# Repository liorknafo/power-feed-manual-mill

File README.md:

# power-feed-manual-mill

A stepper-motor X-axis power feed for a **SIEG X3.5D** mill.

## Features
- **Speed:** a speed dial and an OLED showing mm/min.
- **Mode switch** (3 positions): LEFT, STOP, RIGHT.
- **Rapid traverse button.**
- **Clutch:** a home-made **electromagnetic tooth clutch**. With the switch on STOP the handwheel turns freely, as it does with no power.
- **Safety:**
  - a hardware E-stop interlock;
  - limit switches;
  - stall detection from an encoder on the leadscrew.

## What is where

| Folder | What | Start here |
|---|---|---|
| `docs/` | The spec, plus notes about the mill | `docs/design.md`, `docs/mill.md` |
| `hardware/` | KiCad 9 schematic + 4-layer 100×100 mm PCB, order files | `hardware/README.md`, `hardware/fab/README.md` |
| `firmware/` | Rust firmware for the RP2040 (Embassy). Core logic is unit-tested on the PC | `firmware/README.md` |
| `mechanical/solidcraft/` | The CAD, in SolidCraft: one parametric design per part, the clutch and feed-unit assemblies, checks, renders, the mains tray's flat patterns | `mechanical/README.md`, `mechanical/solidcraft/README.md` |
| `mechanical/clutch/` | Tooth clutch: machining sheet | `mechanical/clutch/MACHINING.md` |
| `mechanical/feed_unit/` | The whole power feed in one box at the left table end: plate, 2:1 belt, leadscrew stub, encoder, clutch module, motor, controller PCB and control panel | `mechanical/feed_unit/FEED_UNIT.md` |

## Status

| Part | State |
|---|---|
| Schematic | Done: bare RP2040 (flash, crystal, USB-C with ESD, 3.3 V LDO), TMC5160 power stage, clutch driver, E-stop interlock. ERC clean, netlist checked, independently reviewed |
| PCB | **Ready to order.** 4 layers, 100 × 100 mm. Independently reviewed over 4 rounds (power stage, RP2040 layout, assembly). DRC 0 errors with schematic parity (11 cosmetic silkscreen warnings). Gerbers, BOM, CPL in `hardware/fab/` |
| Firmware | Builds for the RP2040; 48 passing tests. Flashable with the box closed: **USB FLASH** menu item + end-wall USB-C (UF2), or the end-wall SWD port with a Debug Probe (recovers anything). Needs bench commissioning (`firmware/README.md`) |
| CAD | In SolidCraft (`mechanical/solidcraft/`), migrated from the build123d model part by part and checked against it (identical apart from true arcs where the old model used polylines, and real bends in the sheet-metal tray). Interference, mains separation, door swing and print fit re-checked in SolidCraft |
| Clutch CAD | Ready to machine, after you measure the motor shaft length. Independently reviewed for fit and for machinability on a 3-axis CNC + manual lathe/mill (teeth: one 60° chamfer-mill pass per flank). Magnetic sizing must be bench-calibrated |
| Feed unit CAD | Structure reviewed: Oldham drive, circlip bearing stack, encoder adapter, guard, drawbolt tensioner. **Mill-side dimensions are placeholders until measured** |
| Housing (one box: drive + PCB + controls + 36 V supply) | **Ready to print.** Compact, rounded PETG (116 × 204 × 262 mm), built-in LRS-150-36 supply (the only 36 V Mean Well on Amazon that ships to Israel) and fused, switched IEC inlet in an earthed aluminium mains tray (mains part independently safety-reviewed: wiring room, separation, fixing, earthing, assembly order); USB-C, BOOT/RESET and SWD on the end wall: a shell, a hood with the controls, a bottom door (the clutch/motor module and the mains tray go in and come out from below) and an end cap that slides on last and holds the door's far end, each one print on a Prusa MK3S with no supports; the PCB lies above the motor. Independently reviewed (printability, assembly, tool access, plugs, inserts). See FEED_UNIT.md → "Housing" |

## What you need to do

1. **Measure the mill** (`docs/mill.md` → "Unknown"):
   - leadscrew pitch;
   - the left leadscrew end and its drive slot;
   - where the plate can bolt to the table end;
   - clearances at full travel.

   Enter the values in the SolidCraft part files that use them (`mechanical/solidcraft/README.md` → "Measure first"
   lists each value's parameter and files), update the assemblies' links and run the checks.
2. **Measure the motor:** shaft length beyond the flange and the pilot diameter. Set `shaft_len` and `pilot_d` the same way.
3. **Order the PCB:**
   - upload `hardware/fab/power-feed-gerbers.zip` to JLCPCB: 4 layers, 1.6 mm, 1 oz outer copper (standard; 2 oz breaks the fine-pitch spacing);
   - stencil plus the BOM/CPL for assembly, or reflow it yourself;
   - everything is SMD on the top side, including the RP2040 (QFN-56, 0.4 mm pitch: use the stencil);
   - hand-solder only the SWD header J3, and trim its pins flush underneath (they face the motor);
   - USB-C (J4) shell pegs: solder from below with little solder, fit the panel IDC header J6 last and check it sits flat.
4. **Make the clutch** (`MACHINING.md`). Check the mated teeth (pole gap 0.15 ± 0.05), then calibrate on the bench: pull force and
   cam-out torque against hold current.
5. **Print the housing** (shell + hood, PETG on the MK3S; `FEED_UNIT.md` → "Housing") and machine the feed-unit parts (`FEED_UNIT.md`).
6. **Flash and commission:** follow `firmware/README.md` → *Commissioning*, in order, before mounting on the mill.

## Rebuilding things
```sh
python3 hardware/tools/check_schematic.py                 # schematic: ERC + netlist check
python3 hardware/tools/check_pcb.py                       # PCB: DRC + schematic parity
(cd firmware/feed-core && cargo test)                     # logic tests
(cd firmware/feed-app && cargo build --release)           # firmware
(cd mechanical/solidcraft && solidcraft-cli run clutch.build.json --save clutch.sc)        # clutch assembly
(cd mechanical/solidcraft && solidcraft-cli run feed_unit.build.json --save feed_unit.sc)  # whole unit
python3 mechanical/solidcraft/tools/check.py        # interference (clutch engaged + released), mains separation, door, print fit
sh mechanical/solidcraft/tools/render.sh            # renders
```

The CAD needs SolidCraft 0.40 or later (`solidcraft-cli` on the PATH); edit the parts in the SolidCraft app.

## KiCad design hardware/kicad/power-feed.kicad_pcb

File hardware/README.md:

# Hardware — controller PCB

```
hardware/
  tools/build_schematic.py   circuit description (source of truth for now)
  tools/kicad_gen.py         generator: Python parts/nets -> KiCad 9 schematic
  tools/check_schematic.py   ERC + netlist-vs-intent + footprint check
  tools/sexp.py              S-expression reader/writer
  kicad/                     generated KiCad project (open power-feed.kicad_pro)
```

## Regenerate and check

```sh
python3 hardware/tools/check_schematic.py    # builds, runs KiCad ERC, compares netlist
```

The check:
- runs KiCad's ERC and fails on any error not in the reviewed allow-list;
- exports the netlist and requires every net to match the intended connections exactly;
- lists parts whose footprint is missing.

## How the generated sheets look

Every pin gets a short wire stub and a net label; there are no long wires. Connectivity therefore comes only from net names, which keeps the generated schematic correct by construction. Labels used on more than one sheet are global labels; power nets use power symbols.

## Workflow

While the circuit is still changing, edit `build_schematic.py` and regenerate. Edits made in the KiCad GUI are overwritten on regeneration. Once the circuit is frozen for layout, stop regenerating, and from then on edit the schematic in KiCad directly.

Sheets: power input and 5 V buck · TMC5160 driver · RP2040 (flash, crystal, USB-C, 3.3 V LDO) and E-stop interlock · clutch driver · panel I/O. See `docs/design.md` §4 for the pin map and §7.6 for the clutch driver.

## PCB

```sh
KPY=/Applications/KiCad/KiCad.app/Contents/Frameworks/Python.framework/Versions/Current/bin/python3
$KPY hardware/tools/build_pcb.py --route   # place, planes, Freerouting, power pours, GND stitching
$KPY hardware/tools/fix_planes.py          # vias to planes for anything the router left
$KPY hardware/tools/finish_pcb.py          # bridge pours for the last same-net gaps
$KPY hardware/tools/manual_fixes.py        # hand re-routes of the spots the scripts could not close (documented inside)
$KPY hardware/tools/silk_cleanup.py        # passives' refs to F.Fab, relocate the rest, connector labels + title
python3 hardware/tools/check_pcb.py        # KiCad DRC + schematic parity
python3 hardware/tools/export_fab.py       # Gerbers, drills, BOM, CPL, zip -> hardware/fab/
hardware/tools/render_pcb.sh               # 2D layer PNGs; 3D: kicad-cli pcb render
```

The saved `kicad/power-feed.kicad_pcb` is the master now: `build_pcb.py` rebuilds from scratch and throws away
the routing, so do not rerun it unless the schematic changes. `manual_fixes.py` and `silk_cleanup.py` are
idempotent and only touch the items they describe.

- **Board:** 100×100 mm, 4 layers: F.Cu signals + GND pour, In1 GND plane, In2 split +36V (power area) / +3V3, B.Cu signals + GND pour.
- **Autorouter:** Freerouting 2.4.1, run on Java 25. Set `FREEROUTING_JAR` to point at your copy.
- **Order** with standard 1 oz outer copper: the widths are sized for 1 oz at ~3.5 A RMS motor phases, and 2 oz would break the 0.15 mm fine-pitch spacing.

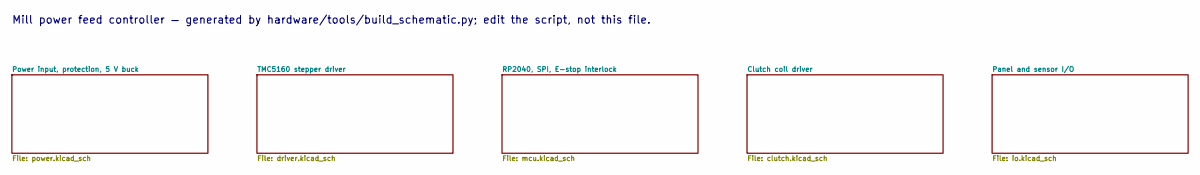
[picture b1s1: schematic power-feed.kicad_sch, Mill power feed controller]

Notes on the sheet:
Mill power feed controller — generated by hardware/tools/build_schematic.py; edit the script, not this file.

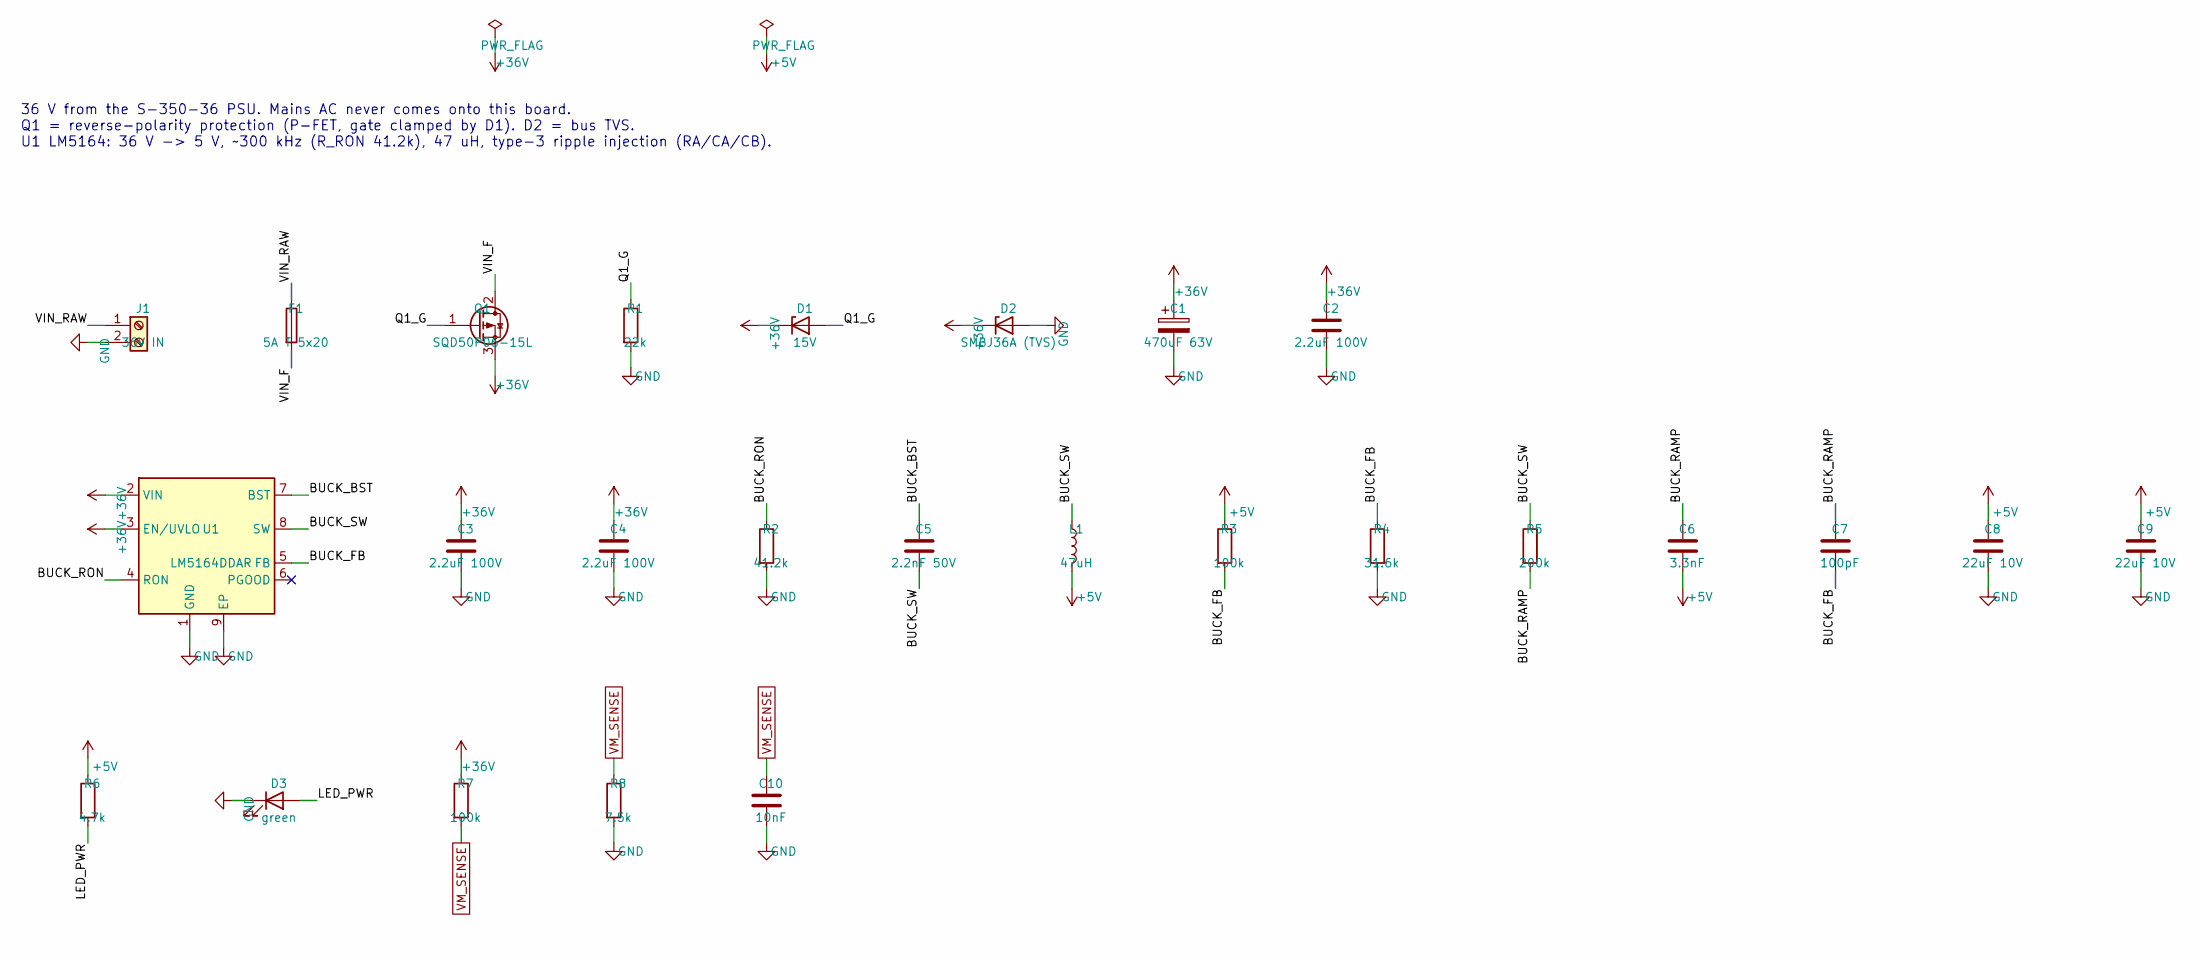
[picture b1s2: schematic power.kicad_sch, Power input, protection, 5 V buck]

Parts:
C1: 470uF 63V; CP_Radial_D12.5mm_P5.00mm; MPN Panasonic EEUFR1J471; LCSC C407954
C2, C3, C4: 2.2uF 100V; C_1210_3225Metric; MPN Murata GRM32ER72A225KA35L; LCSC C86054
C5: 2.2nF 50V; C_0603_1608Metric; MPN FH 0603B222K500NT; LCSC C1604
C6: 3.3nF; C_0603_1608Metric; MPN Samsung CL10B332KB8NNNC; LCSC C1613
C7: 100pF; C_0603_1608Metric; MPN Samsung CL10C101JB8NNNC; LCSC C14858
C8, C9: 22uF 10V; C_1206_3216Metric; MPN Samsung CL31A226KAHNNNE; LCSC C12891
C10: 10nF; C_0603_1608Metric; MPN FH 0603B103K500NT; LCSC C57112
D1: 15V; D_SOD-123; MPN onsemi MMSZ5245BT1G; LCSC C129730
D2: SMBJ36A (TVS); D_SMB; MPN SMBJ36A; LCSC C114001
D3: green; LED_0603_1608Metric; MPN KENTO KT-0603G; LCSC C12624
F1: 5A T 5x20; Fuseholder_XC_BLX-A_5x20mm_P22.00mm; MPN BLX-A holder + Littelfuse 0215005.MXP (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; LCSC C3131
J1: 36V IN; PhoenixContact_MSTBA_2,5_2-G-5,08_1x02_P5.08mm_Horizontal; MPN KF2EDGR-5.08-2P (+ plug KF2EDGK-5.08-2P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; LCSC C441204
L1: 47uH; L_TDK_VLS6045EX_VLS6045AF; MPN TDK VLS6045EX-470M; LCSC C404505
Q1: SQD50P06-15L; TO-252-2; MPN SQD50P06-15L_GE3; LCSC C3281500
R1: 22k; R_0603_1608Metric; MPN UNI-ROYAL 0603WAF2202T5E; LCSC C31850
R2: 41.2k; R_0603_1608Metric; MPN FOJAN FRC0603F4122TS; LCSC C2930101
R3, R7: 100k; R_0603_1608Metric; MPN UNI-ROYAL 0603WAF1003T5E; LCSC C25803
R4: 31.6k; R_0603_1608Metric; MPN UNI-ROYAL 0603WAF3162T5E; LCSC C25967
R5: 200k; R_0603_1608Metric; MPN UNI-ROYAL 0603WAF2003T5E; LCSC C25811
R6: 4.7k; R_0603_1608Metric; MPN UNI-ROYAL 0603WAF4701T5E; LCSC C23162
R8: 7.5k; R_0603_1608Metric; MPN UNI-ROYAL 0603WAF7501T5E; LCSC C23234
U1: LM5164DDAR; HSOP-8-1EP_3.9x4.9mm_P1.27mm_EP2.41x3.1mm_ThermalVias; MPN LM5164DDAR; LCSC C477928

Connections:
+5V: C6.2, C8.1, C9.1, L1.2, R3.1, R6.1; also elsewhere on the board
+36V: C1.1, C2.1, C3.1, C4.1, D1.1 (K), D2.1 (K), Q1.3 (S), R7.1, U1.2 (VIN), U1.3 (EN/UVLO); also elsewhere on the board
/Power input, protection, 5 V buck/BUCK_BST: C5.1, U1.7 (BST)
/Power input, protection, 5 V buck/BUCK_FB: C7.2, R3.2, R4.1, U1.5 (FB)
/Power input, protection, 5 V buck/BUCK_RAMP: C6.1, C7.1, R5.2
/Power input, protection, 5 V buck/BUCK_RON: R2.1, U1.4 (RON)
/Power input, protection, 5 V buck/BUCK_SW: C5.2, L1.1, R5.1, U1.8 (SW)
/Power input, protection, 5 V buck/LED_PWR: D3.2 (A), R6.2
/Power input, protection, 5 V buck/Q1_G: D1.2 (A), Q1.1 (G), R1.1
/Power input, protection, 5 V buck/VIN_F: F1.2, Q1.2 (D)
/Power input, protection, 5 V buck/VIN_RAW: F1.1, J1.1
GND: C1.2, C2.2, C3.2, C4.2, C8.2, C9.2, C10.2, D2.2 (A), D3.1 (K), J1.2, R1.2, R2.2, R4.2, R8.2, U1.1 (GND), U1.9 (EP); also elsewhere on the board
VM_SENSE: C10.1, R7.2, R8.1; also elsewhere on the board

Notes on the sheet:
36 V from the S-350-36 PSU. Mains AC never comes onto this board. Q1 = reverse-polarity protection (P-FET, gate clamped by D1). D2 = bus TVS. U1 LM5164: 36 V -> 5 V, ~300 kHz (R_RON 41.2k), 47 uH, type-3 ripple injection (RA/CA/CB).

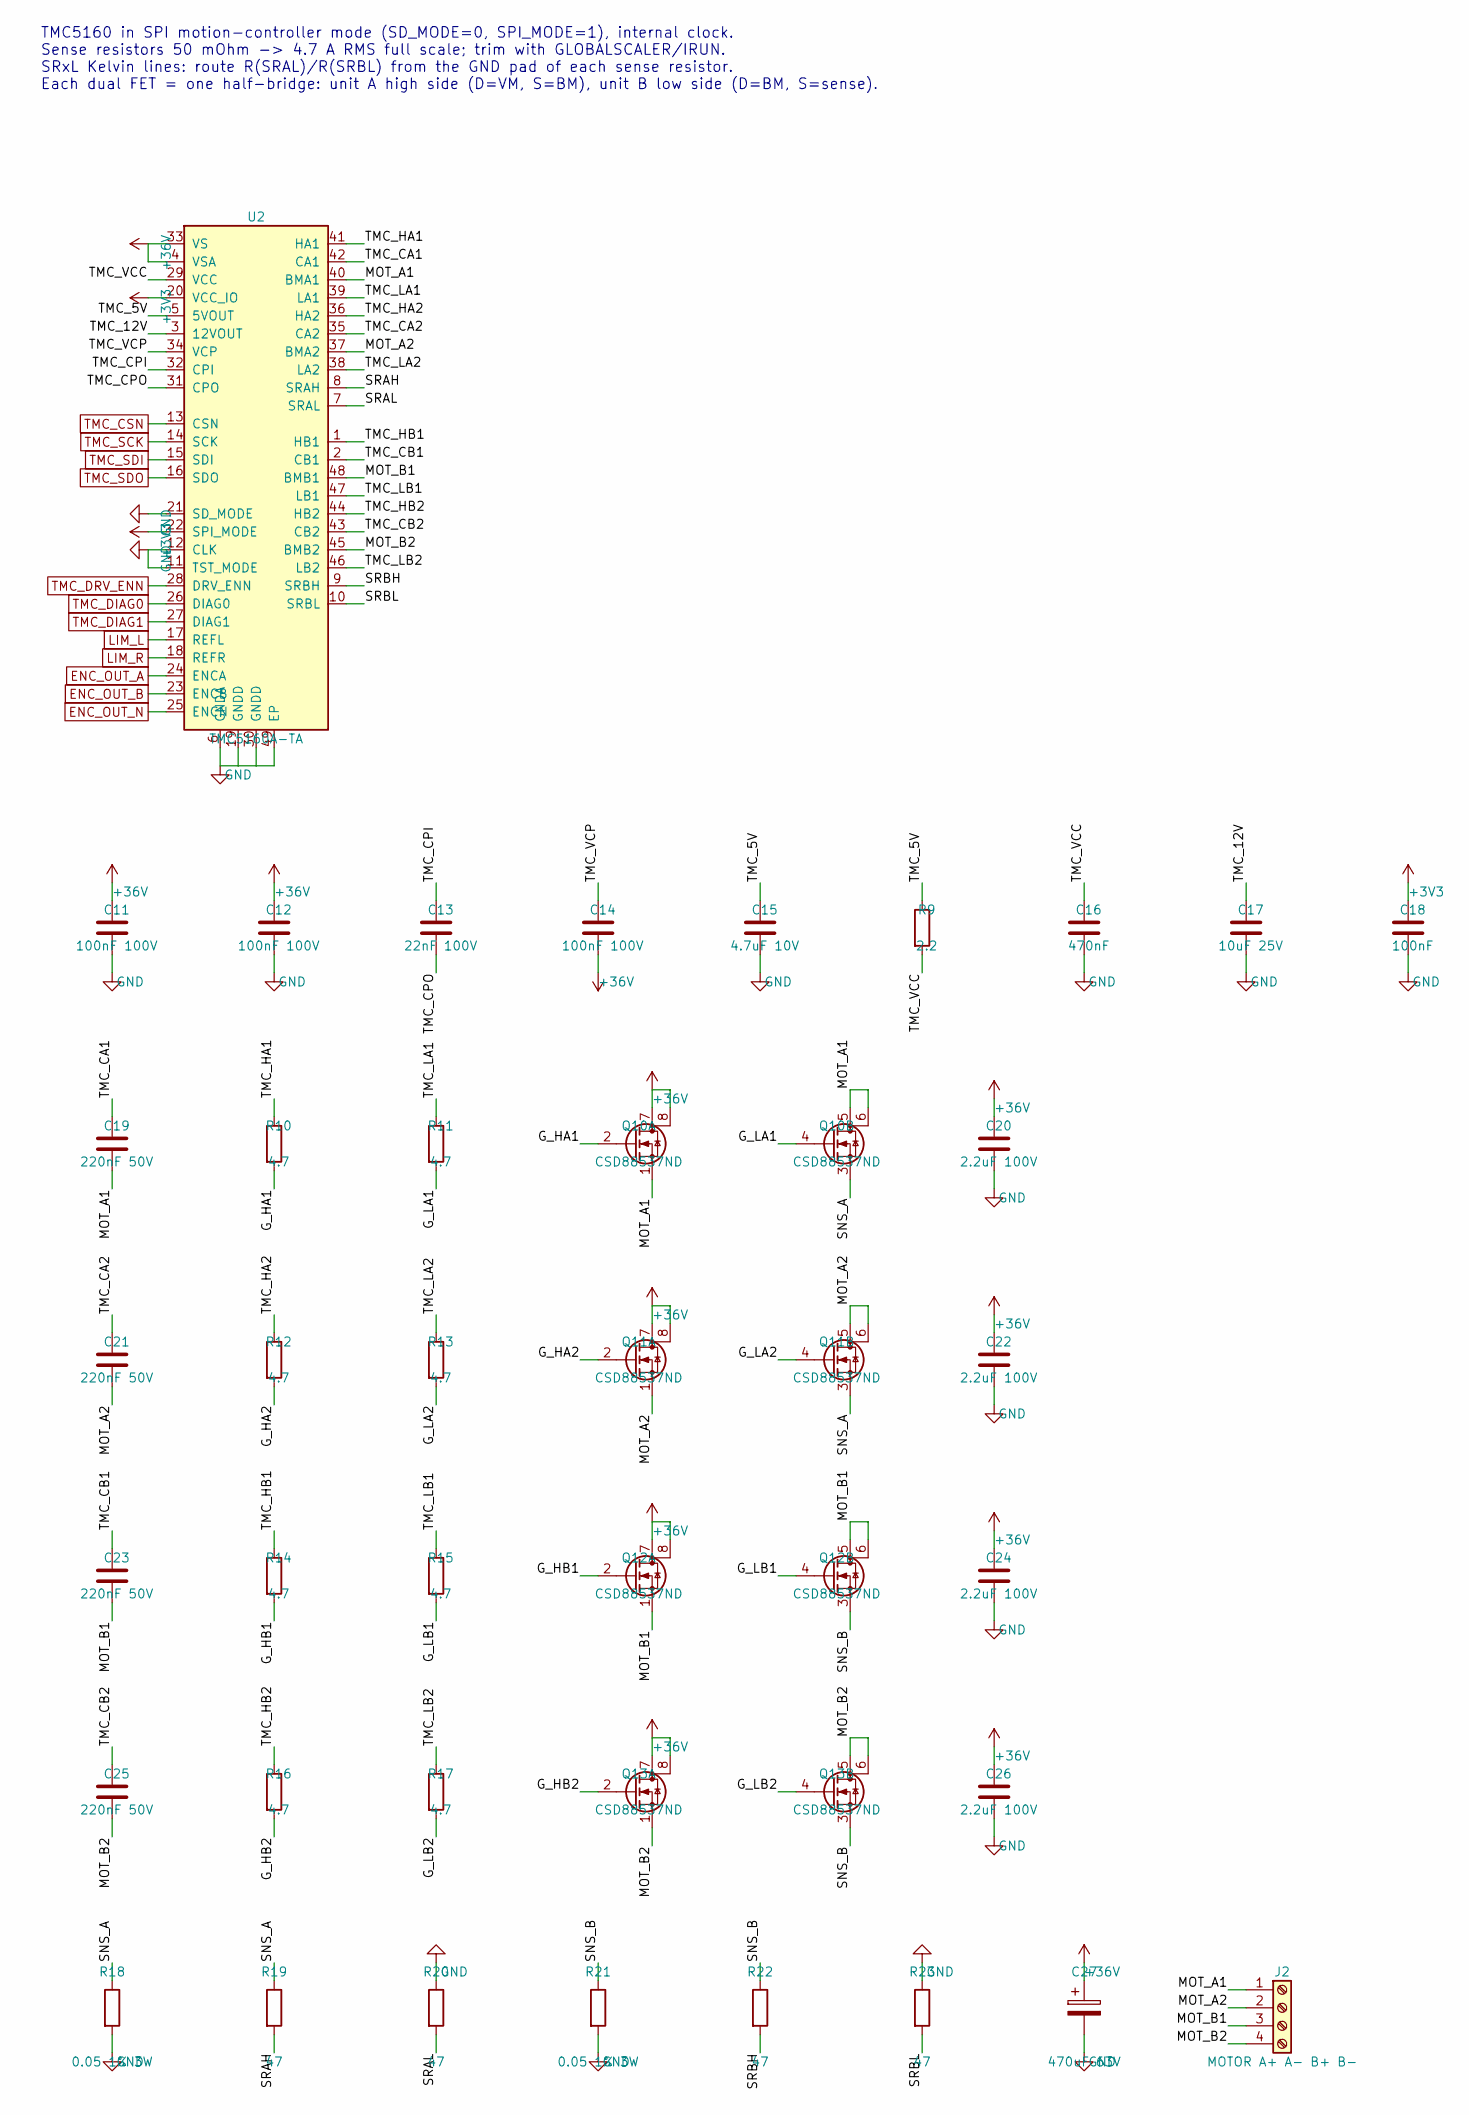
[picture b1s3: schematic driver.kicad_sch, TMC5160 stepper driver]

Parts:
C11, C12, C14: 100nF 100V; C_0805_2012Metric; MPN Samsung CL21B104KCFNNNE; LCSC C28233
C13: 22nF 100V; C_0805_2012Metric; MPN Yageo CC0805KRX7R0BB223; LCSC C107137
C15: 4.7uF 10V; C_0805_2012Metric; MPN Samsung CL21A475KAQNNNE; LCSC C1779
C16: 470nF; C_0603_1608Metric; MPN Samsung CL10B474KA8NNNC; LCSC C1623
C17: 10uF 25V; C_1206_3216Metric; MPN Samsung CL31A106KBHNNNE; LCSC C13585
C18: 100nF; C_0603_1608Metric; MPN Yageo CC0603KRX7R9BB104; LCSC C14663
C19, C21, C23, C25: 220nF 50V; C_0603_1608Metric; MPN Samsung CL10B224KB8NNNC; LCSC C64705
C20, C22, C24, C26: 2.2uF 100V; C_1210_3225Metric; MPN Murata GRM32ER72A225KA35L; LCSC C86054
C27: 470uF 63V; CP_Radial_D12.5mm_P5.00mm; MPN Panasonic EEUFR1J471; LCSC C407954
J2: MOTOR A+ A- B+ B-; PhoenixContact_MSTBA_2,5_4-G-5,08_1x04_P5.08mm_Horizontal; MPN KF2EDGR-5.08-4P (+ plug KF2EDGK-5.08-4P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; LCSC C441206
Q10, Q11, Q12, Q13: CSD88537ND; SOIC-8_3.9x4.9mm_P1.27mm; MPN CSD88537ND; LCSC C117439
R9: 2.2; R_0603_1608Metric; MPN UNI-ROYAL 0603WAF220KT5E; LCSC C22939
R10, R11, R12, R13, R14, R15, R16, R17: 4.7; R_0402_1005Metric; MPN UNI-ROYAL 0402WGF470KTCE; LCSC C25121
R18, R21: 0.05 1% 3W; R_2512_6332Metric; MPN CSM2512FT50L0; LCSC C346860
R19, R20, R22, R23: 47; R_0603_1608Metric; MPN UNI-ROYAL 0603WAF470JT5E; LCSC C23182
U2: TMC5160A-TA; TQFP-48-1EP_7x7mm_P0.5mm_EP5x5mm_ThermalVias; LCSC C516354

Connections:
+3V3: C18.1, U2.20 (VCC_IO), U2.22 (SPI_MODE); also elsewhere on the board
+36V: C11.1, C12.1, C14.2, C20.1, C22.1, C24.1, C26.1, C27.1, Q10.7 (D), Q10.8 (D), Q11.7 (D), Q11.8 (D), Q12.7 (D), Q12.8 (D), Q13.7 (D), Q13.8 (D), U2.4 (VSA), U2.33 (VS); also elsewhere on the board
/TMC5160 stepper driver/G_HA1: Q10.2 (G), R10.2
/TMC5160 stepper driver/G_HA2: Q11.2 (G), R12.2
/TMC5160 stepper driver/G_HB1: Q12.2 (G), R14.2
/TMC5160 stepper driver/G_HB2: Q13.2 (G), R16.2
/TMC5160 stepper driver/G_LA1: Q10.4 (G), R11.2
/TMC5160 stepper driver/G_LA2: Q11.4 (G), R13.2
/TMC5160 stepper driver/G_LB1: Q12.4 (G), R15.2
/TMC5160 stepper driver/G_LB2: Q13.4 (G), R17.2
/TMC5160 stepper driver/MOT_A1: C19.2, J2.1, Q10.1 (S), Q10.5 (D), Q10.6 (D), U2.40 (BMA1)
/TMC5160 stepper driver/MOT_A2: C21.2, J2.2, Q11.1 (S), Q11.5 (D), Q11.6 (D), U2.37 (BMA2)
/TMC5160 stepper driver/MOT_B1: C23.2, J2.3, Q12.1 (S), Q12.5 (D), Q12.6 (D), U2.48 (BMB1)
/TMC5160 stepper driver/MOT_B2: C25.2, J2.4, Q13.1 (S), Q13.5 (D), Q13.6 (D), U2.45 (BMB2)
/TMC5160 stepper driver/SNS_A: Q10.3 (S), Q11.3 (S), R18.1, R19.1
/TMC5160 stepper driver/SNS_B: Q12.3 (S), Q13.3 (S), R21.1, R22.1
/TMC5160 stepper driver/SRAH: R19.2, U2.8 (SRAH)
/TMC5160 stepper driver/SRAL: R20.2, U2.7 (SRAL)
/TMC5160 stepper driver/SRBH: R22.2, U2.9 (SRBH)
/TMC5160 stepper driver/SRBL: R23.2, U2.10 (SRBL)
/TMC5160 stepper driver/TMC_5V: C15.1, R9.1, U2.5 (5VOUT)
/TMC5160 stepper driver/TMC_12V: C17.1, U2.3 (12VOUT)
/TMC5160 stepper driver/TMC_CA1: C19.1, U2.42 (CA1)
/TMC5160 stepper driver/TMC_CA2: C21.1, U2.35 (CA2)
/TMC5160 stepper driver/TMC_CB1: C23.1, U2.2 (CB1)
/TMC5160 stepper driver/TMC_CB2: C25.1, U2.43 (CB2)
/TMC5160 stepper driver/TMC_CPI: C13.1, U2.32 (CPI)
/TMC5160 stepper driver/TMC_CPO: C13.2, U2.31 (CPO)
/TMC5160 stepper driver/TMC_HA1: R10.1, U2.41 (HA1)
/TMC5160 stepper driver/TMC_HA2: R12.1, U2.36 (HA2)
/TMC5160 stepper driver/TMC_HB1: R14.1, U2.1 (HB1)
/TMC5160 stepper driver/TMC_HB2: R16.1, U2.44 (HB2)
/TMC5160 stepper driver/TMC_LA1: R11.1, U2.39 (LA1)
/TMC5160 stepper driver/TMC_LA2: R13.1, U2.38 (LA2)
/TMC5160 stepper driver/TMC_LB1: R15.1, U2.47 (LB1)
/TMC5160 stepper driver/TMC_LB2: R17.1, U2.46 (LB2)
/TMC5160 stepper driver/TMC_VCC: C16.1, R9.2, U2.29 (VCC)
/TMC5160 stepper driver/TMC_VCP: C14.1, U2.34 (VCP)
ENC_OUT_A: U2.24 (ENCA); also elsewhere on the board
ENC_OUT_B: U2.23 (ENCB); also elsewhere on the board
ENC_OUT_N: U2.25 (ENCN); also elsewhere on the board
GND: C11.2, C12.2, C15.2, C16.2, C17.2, C18.2, C20.2, C22.2, C24.2, C26.2, C27.2, R18.2, R20.1, R21.2, R23.1, U2.6 (GNDA), U2.11 (TST_MODE), U2.12 (CLK), U2.19 (GNDD), U2.21 (SD_MODE), U2.30 (GNDD), U2.49 (EP); also elsewhere on the board
LIM_L: U2.17 (REFL); also elsewhere on the board
LIM_R: U2.18 (REFR); also elsewhere on the board
TMC_CSN: U2.13 (CSN); also elsewhere on the board
TMC_DIAG0: U2.26 (DIAG0); also elsewhere on the board
TMC_DIAG1: U2.27 (DIAG1); also elsewhere on the board
TMC_DRV_ENN: U2.28 (DRV_ENN); also elsewhere on the board
TMC_SCK: U2.14 (SCK); also elsewhere on the board
TMC_SDI: U2.15 (SDI); also elsewhere on the board
TMC_SDO: U2.16 (SDO); also elsewhere on the board

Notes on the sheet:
TMC5160 in SPI motion-controller mode (SD_MODE=0, SPI_MODE=1), internal clock. Sense resistors 50 mOhm -> 4.7 A RMS full scale; trim with GLOBALSCALER/IRUN. SRxL Kelvin lines: route R(SRAL)/R(SRBL) from the GND pad of each sense resistor. Each dual FET = one half-bridge: unit A high side (D=VM, S=B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

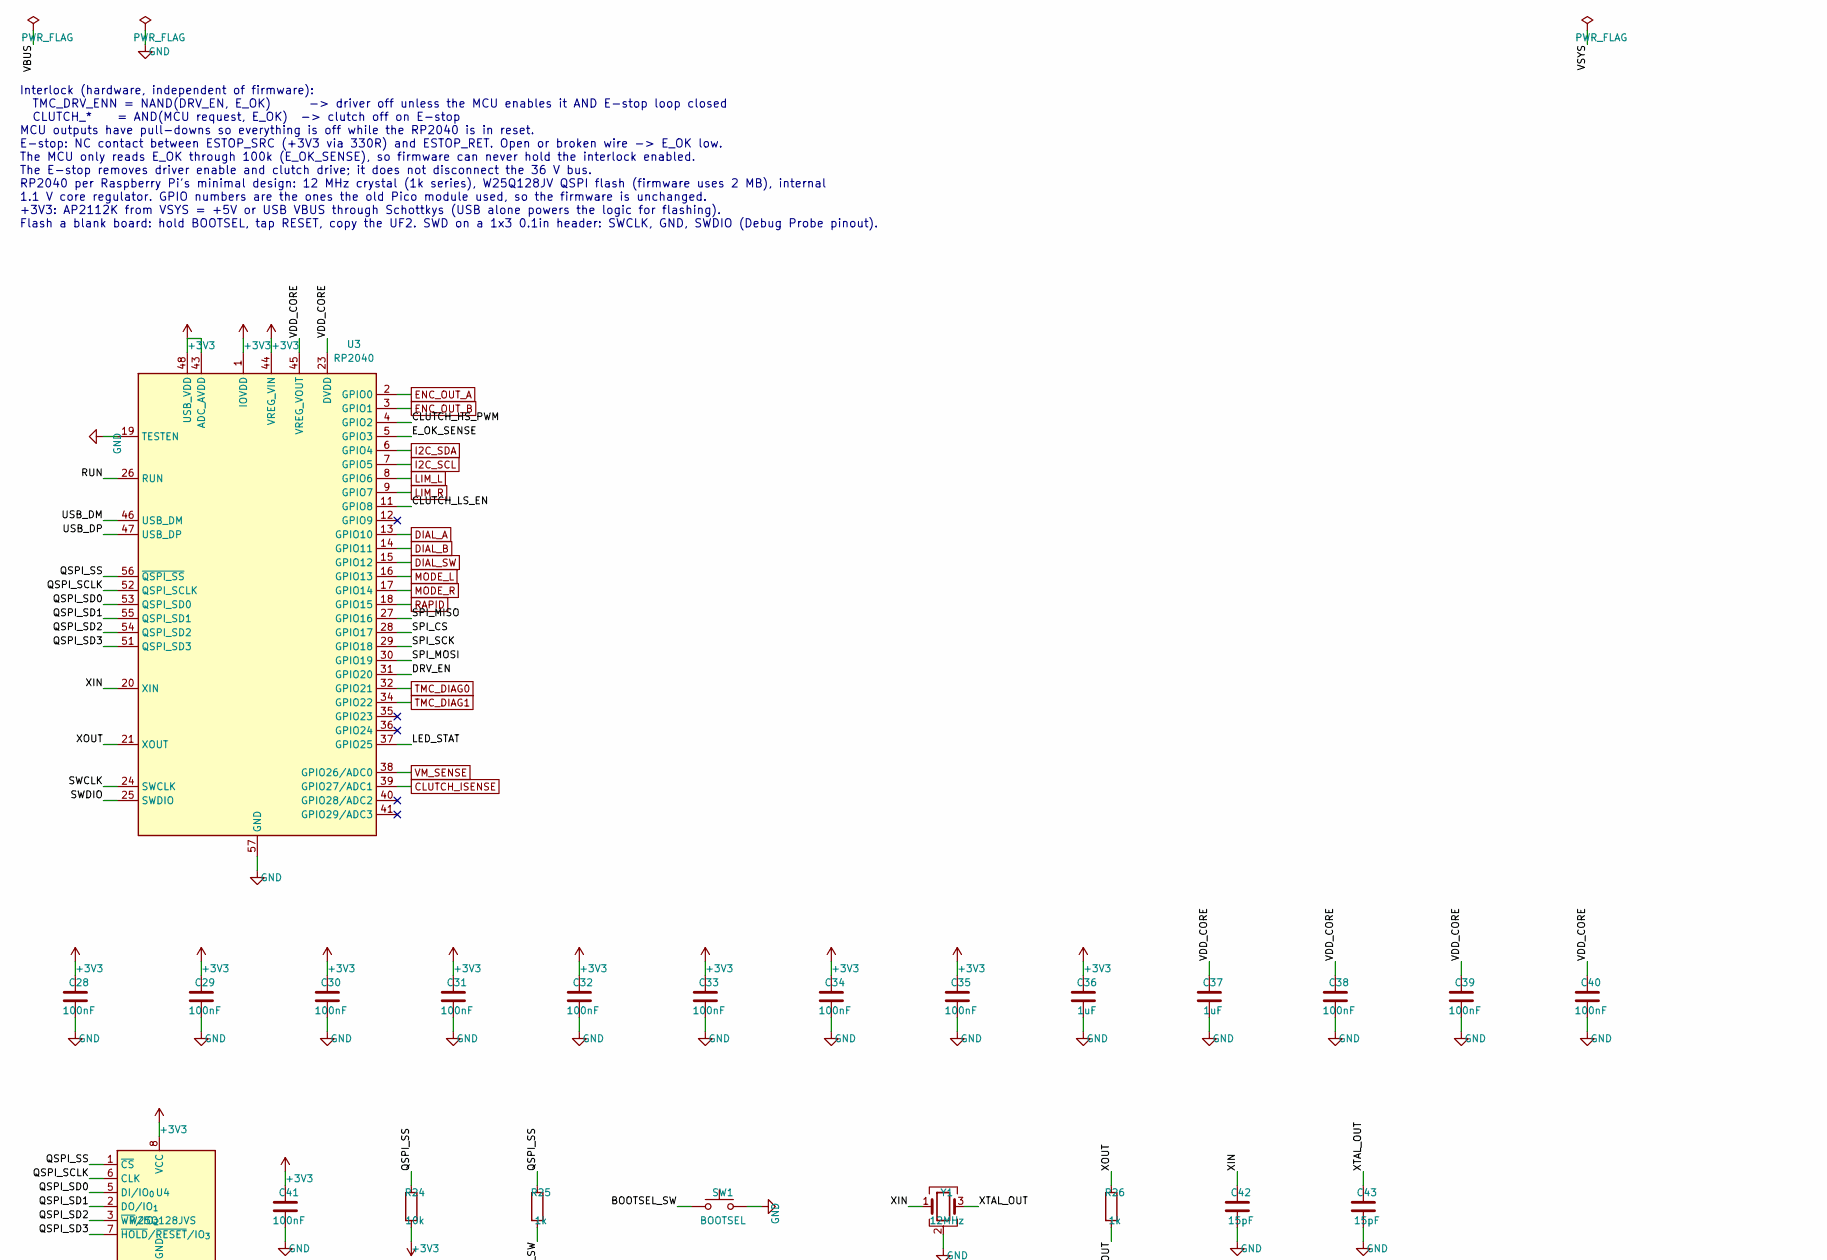
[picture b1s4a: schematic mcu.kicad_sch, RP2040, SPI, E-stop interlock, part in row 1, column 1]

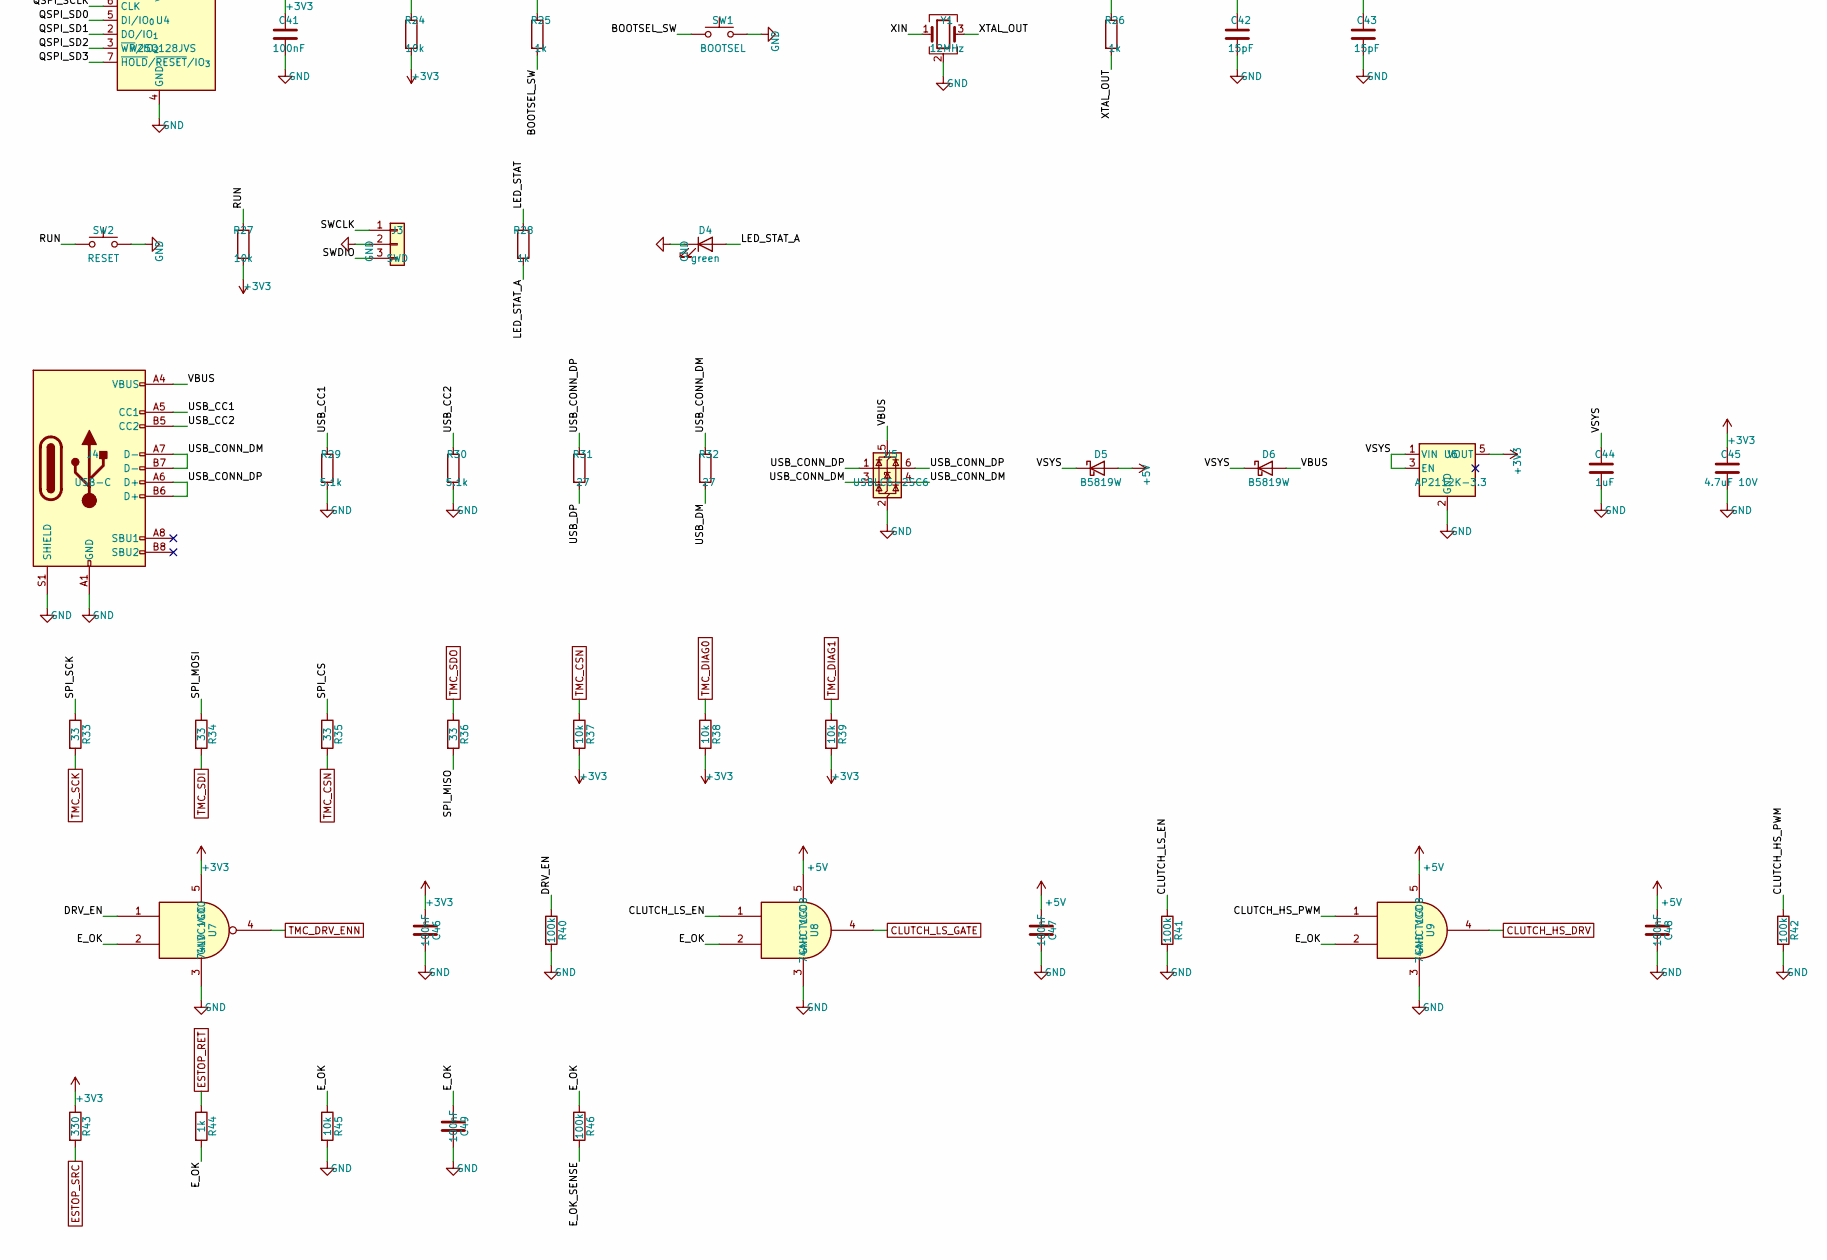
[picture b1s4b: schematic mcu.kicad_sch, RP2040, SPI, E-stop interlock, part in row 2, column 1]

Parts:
C28, C29, C30, C31, C32, C33, C34, C35, C38, C39, C40, C41, C46, C47, C48, C49: 100nF; C_0603_1608Metric; MPN Yageo CC0603KRX7R9BB104; LCSC C14663
C36, C37, C44: 1uF; C_0603_1608Metric; MPN Samsung CL10A105KB8NNNC; LCSC C15849
C42, C43: 15pF; C_0603_1608Metric; MPN Samsung CL10C150JB8NNNC; LCSC C1644
C45: 4.7uF 10V; C_0805_2012Metric; MPN Samsung CL21A475KAQNNNE; LCSC C1779
D4: green; LED_0603_1608Metric; MPN KENTO KT-0603G; LCSC C12624
D5, D6: B5819W; D_SOD-123; MPN Changjing B5819W SL; LCSC C8598
J3: SWD; PinHeader_1x03_P2.54mm_Vertical; MPN 2.54 mm 1x3 male header, hand-solder (D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
J4: USB-C; USB_C_Receptacle_HRO_TYPE-C-31-M-12; MPN HRO TYPE-C-31-M-12; LCSC C165948
R24, R27, R37, R38, R39, R45: 10k; R_0603_1608Metric; MPN UNI-ROYAL 0603WAF1002T5E; LCSC C25804
R25, R26, R28, R44: 1k; R_0603_1608Metric; MPN UNI-ROYAL 0603WAF1001T5E; LCSC C21190
R29, R30: 5.1k; R_0603_1608Metric; MPN UNI-ROYAL 0603WAF5101T5E; LCSC C23186
R31, R32: 27; R_0603_1608Metric; MPN UNI-ROYAL 0603WAF270JT5E; LCSC C25190
R33, R34, R35, R36: 33; R_0603_1608Metric; MPN UNI-ROYAL 0603WAF330JT5E; LCSC C23140
R40, R41, R42, R46: 100k; R_0603_1608Metric; MPN UNI-ROYAL 0603WAF1003T5E; LCSC C25803
R43: 330; R_0603_1608Metric; MPN UNI-ROYAL 0603WAF3300T5E; LCSC C23138
SW1: BOOTSEL; SW_SPST_B3S-1000; MPN Omron B3S-1000; LCSC C2733655
SW2: RESET; SW_SPST_B3S-1000; MPN Omron B3S-1000; LCSC C2733655
U3: RP2040; QFN-56-1EP_7x7mm_P0.4mm_EP3.2x3.2mm_ThermalVias; MPN Raspberry Pi RP2040; LCSC C2040
U4: W25Q128JVS; SOIC-8_5.3x5.3mm_P1.27mm; MPN Winbond W25Q128JVSIQ (W25Q16 is out of 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; LCSC C113767
U5: USBLC6-2SC6; SOT-23-6; MPN STMicroelectronics USBLC6-2SC6; LCSC C7519
U6: AP2112K-3.3; SOT-23-5; MPN Diodes AP2112K-3.3TRG1; LCSC C51118
U7: 74LVC1G00; SOT-23-5; MPN SN74LVC1G00DBVR; LCSC C7826
U8, U9: 74AHCT1G08; SOT-23-5; MPN SN74AHCT1G08DBVR; LCSC C113521
Y1: 12MHz; Crystal_SMD_3225-4Pin_3.2x2.5mm; MPN Abracon ABM8-272-T3 (12 MHz, CL 10 pF, 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; LCSC C20625731

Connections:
+3V3: C28.1, C29.1, C30.1, C31.1, C32.1, C33.1, C34.1, C35.1, C36.1, C41.1, C45.1, C46.1, R24.2, R27.2, R37.2, R38.2, R39.2, R43.1, U3.1 (IOVDD), U3.10 (IOVDD), U3.22 (IOVDD), U3.33 (IOVDD), U3.42 (IOVDD), U3.43 (ADC_AVDD), U3.44 (VREG_VIN), U3.48 (USB_VDD), U3.49 (IOVDD), U4.8 (VCC), U6.5 (VOUT), U7.5 (VCC); also elsewhere on the board
+5V: C47.1, C48.1, D5.2 (A), U8.5 (VCC), U9.5 (VCC); also elsewhere on the board
/RP2040, SPI, E-stop interlock/BOOTSEL_SW: R25.2, SW1.1
/RP2040, SPI, E-stop interlock/CLUTCH_HS_PWM: R42.1, U3.4 (GPIO2), U9.1
/RP2040, SPI, E-stop interlock/CLUTCH_LS_EN: R41.1, U3.11 (GPIO8), U8.1
/RP2040, SPI, E-stop interlock/DRV_EN: R40.1, U3.31 (GPIO20), U7.1
/RP2040, SPI, E-stop interlock/E_OK: C49.1, R44.2, R45.1, R46.1, U7.2, U8.2, U9.2
/RP2040, SPI, E-stop interlock/E_OK_SENSE: R46.2, U3.5 (GPIO3)
/RP2040, SPI, E-stop interlock/LED_STAT: R28.1, U3.37 (GPIO25)
/RP2040, SPI, E-stop interlock/LED_STAT_A: D4.2 (A), R28.2
/RP2040, SPI, E-stop interlock/QSPI_SCLK: U3.52 (QSPI_SCLK), U4.6 (CLK)
/RP2040, SPI, E-stop interlock/QSPI_SD0: U3.53 (QSPI_SD0), U4.5 (DI/IO_{0})
/RP2040, SPI, E-stop interlock/QSPI_SD1: U3.55 (QSPI_SD1), U4.2 (DO/IO_{1})
/RP2040, SPI, E-stop interlock/QSPI_SD2: U3.54 (QSPI_SD2), U4.3 (~WP/IO_{2})
/RP2040, SPI, E-stop interlock/QSPI_SD3: U3.51 (QSPI_SD3), U4.7 (~HOLD/~RESET/IO_{3})
/RP2040, SPI, E-stop interlock/QSPI_SS: R24.1, R25.1, U3.56 (~QSPI_SS), U4.1 (~CS)
/RP2040, SPI, E-stop interlock/RUN: R27.1, SW2.1, U3.26 (RUN)
/RP2040, SPI, E-stop interlock/SPI_CS: R35.1, U3.28 (GPIO17)
/RP2040, SPI, E-stop interlock/SPI_MISO: R36.2, U3.27 (GPIO16)
/RP2040, SPI, E-stop interlock/SPI_MOSI: R34.1, U3.30 (GPIO19)
/RP2040, SPI, E-stop interlock/SPI_SCK: R33.1, U3.29 (GPIO18)
/RP2040, SPI, E-stop interlock/SWCLK: J3.1, U3.24 (SWCLK)
/RP2040, SPI, E-stop interlock/SWDIO: J3.3, U3.25 (SWDIO)
/RP2040, SPI, E-stop interlock/USB_CC1: J4.A5 (CC1), R29.1
/RP2040, SPI, E-stop interlock/USB_CC2: J4.B5 (CC2), R30.1
/RP2040, SPI, E-stop interlock/USB_CONN_DM: J4.A7 (D-), J4.B7 (D-), R32.1, U5.3 (I/O2), U5.4 (I/O2)
/RP2040, SPI, E-stop interlock/USB_CONN_DP: J4.A6 (D+), J4.B6 (D+), R31.1, U5.1 (I/O1), U5.6 (I/O1)
/RP2040, SPI, E-stop interlock/USB_DM: R32.2, U3.46 (USB_DM)
/RP2040, SPI, E-stop interlock/USB_DP: R31.2, U3.47 (USB_DP)
/RP2040, SPI, E-stop interlock/VBUS: D6.2 (A), J4.A4 (VBUS), J4.A9 (VBUS), J4.B4 (VBUS), J4.B9 (VBUS), U5.5 (VBUS)
/RP2040, SPI, E-stop interlock/VDD_CORE: C37.1, C38.1, C39.1, C40.1, U3.23 (DVDD), U3.45 (VREG_VOUT), U3.50 (DVDD)
/RP2040, SPI, E-stop interlock/VSYS: C44.1, D5.1 (K), D6.1 (K), U6.1 (VIN), U6.3 (EN)
/RP2040, SPI, E-stop interlock/XIN: C42.1, U3.20 (XIN), Y1.1
/RP2040, SPI, E-stop interlock/XOUT: R26.1, U3.21 (XOUT)
/RP2040, SPI, E-stop interlock/XTAL_OUT: C43.1, R26.2, Y1.3
CLUTCH_HS_DRV: U9.4; also elsewhere on the board
CLUTCH_ISENSE: U3.39 (GPIO27/ADC1); also elsewhere on the board
CLUTCH_LS_GATE: U8.4; also elsewhere on the board
DIAL_A: U3.13 (GPIO10); also elsewhere on the board
DIAL_B: U3.14 (GPIO11); also elsewhere on the board
DIAL_SW: U3.15 (GPIO12); also elsewhere on the board
ENC_OUT_A: U3.2 (GPIO0); also elsewhere on the board
ENC_OUT_B: U3.3 (GPIO1); also elsewhere on the board
ESTOP_RET: R44.1; also elsewhere on the board
ESTOP_SRC: R43.2; also elsewhere on the board
GND: C28.2, C29.2, C30.2, C31.2, C32.2, C33.2, C34.2, C35.2, C36.2, C37.2, C38.2, C39.2, C40.2, C41.2, C42.2, C43.2, C44.2, C45.2, C46.2, C47.2, C48.2, C49.2, D4.1 (K), J3.2, J4.A1 (GND), J4.A12 (GND), J4.B1 (GND), J4.B12 (GND), J4.S1 (SHIELD), R29.2, R30.2, R40.2, R41.2, R42.2, R45.2, SW1.2, SW2.2, U3.19 (TESTEN), U3.57 (GND), U4.4 (GND), U5.2 (GND), U6.2 (GND), U7.3 (GND), U8.3 (GND), U9.3 (GND), Y1.2 (G), Y1.4 (G); also elsewhere on the board
I2C_SCL: U3.7 (GPIO5); also elsewhere on the board
I2C_SDA: U3.6 (GPIO4); also elsewhere on the board
LIM_L: U3.8 (GPIO6); also elsewhere on the board
LIM_R: U3.9 (GPIO7); also elsewhere on the board
MODE_L: U3.16 (GPIO13); also elsewhere on the board
MODE_R: U3.17 (GPIO14); also elsewhere on the board
RAPID: U3.18 (GPIO15); also elsewhere on the board
TMC_CSN: R35.2, R37.1; also elsewhere on the board
TMC_DIAG0: R38.1, U3.32 (GPIO21); also elsewhere on the board
TMC_DIAG1: R39.1, U3.34 (GPIO22); also elsewhere on the board
TMC_DRV_ENN: U7.4; also elsewhere on the board
TMC_SCK: R33.2; also elsewhere on the board
TMC_SDI: R34.2; also elsewhere on the board
TMC_SDO: R36.1; also elsewhere on the board
VM_SENSE: U3.38 (GPIO26/ADC0); also elsewhere on the board

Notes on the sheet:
Interlock (hardware, independent of firmware): TMC_DRV_ENN = NAND(DRV_EN, E_OK) -> driver off unless the MCU enables it AND E-stop loop closed CLUTCH_* = AND(MCU request, E_OK) -> clutch off on E-stop MCU outputs have pull-downs so everything is off while the RP2040 is in reset. E-stop: NC contact 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
